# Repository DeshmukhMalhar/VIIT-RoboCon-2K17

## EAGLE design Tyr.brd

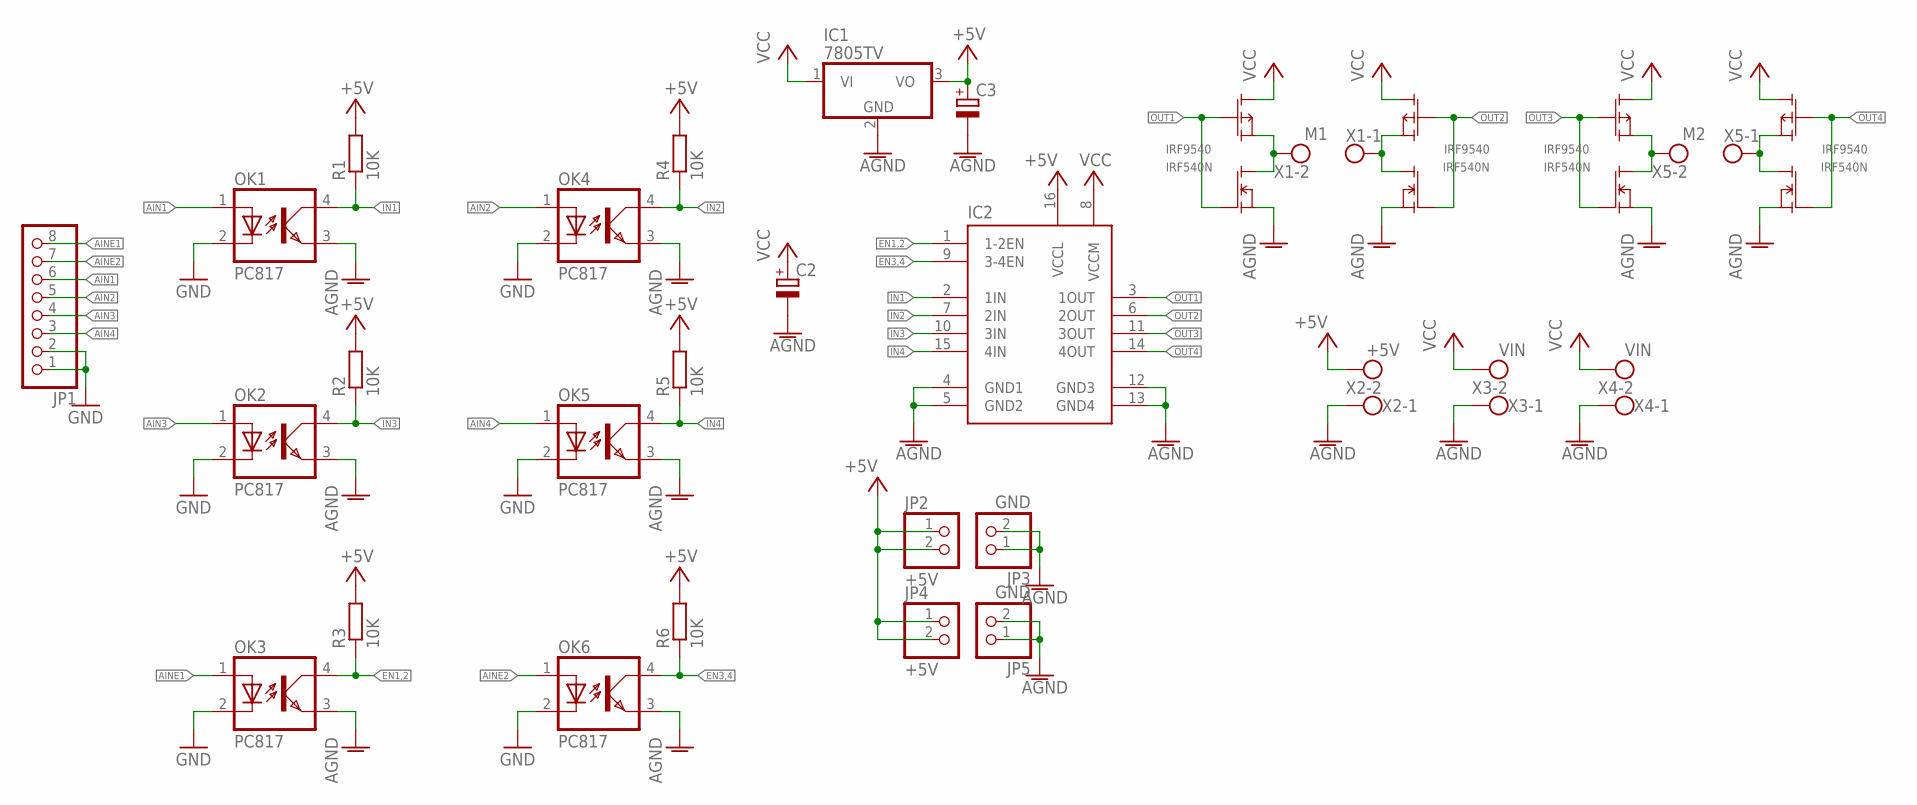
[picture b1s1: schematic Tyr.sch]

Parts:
C2: CPOL-EUE3.5-8; E3,5-8
C3: CPOL-EUE2-5; E2-5
IC1: 7805TV; TO220V
IC2: L293D; DIL16
JP1: PINHD-1X8; 1X08
JP2, JP4: +5V; 1X02
JP3, JP5: GND; 1X02
MOSFET1, MOSFET2, MOSFET3, MOSFET4: IRF540N; IRF9540
OK1, OK2, OK3, OK4, OK5, OK6: PC817; DIL04
P_MOSFET1, P_MOSFET2, P_MOSFET3, P_MOSFET4: IRF9540
R1, R2, R3, R4, R5, R6: 10K; 0207/7
X1: M1; W237-102
X2: +5V; W237-102
X3, X4: VIN; W237-102
X5: M2; W237-102

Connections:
+5V: C3.+, IC1.3 (VO), IC2.16 (VCCL), JP2.1, JP2.2, JP4.1, JP4.2, R1.2, R2.2, R3.2, R4.2, R5.2, R6.2, X2.2
AGND: C2.-, C3.-, IC1.2 (GND), IC2.4 (GND1), IC2.5 (GND2), IC2.12 (GND3), IC2.13 (GND4), JP3.1, JP3.2, JP5.1, JP5.2, MOSFET1.S, MOSFET2.S, MOSFET3.S, MOSFET4.S, OK1.3 (EMIT), OK2.3 (EMIT), OK3.3 (EMIT), OK4.3 (EMIT), OK5.3 (EMIT), OK6.3 (EMIT), X2.1, X3.1, X4.1
AIN1: JP1.6, OK1.1 (A)
AIN2: JP1.5, OK4.1 (A)
AIN3: JP1.4, OK2.1 (A)
AIN4: JP1.3, OK5.1 (A)
AINE1: JP1.8, OK3.1 (A)
AINE2: JP1.7, OK6.1 (A)
EN1,2: IC2.1 (1-2EN), OK3.4 (COL), R3.1
EN3,4: IC2.9 (3-4EN), OK6.4 (COL), R6.1
GND: JP1.1, JP1.2, OK1.2 (C), OK2.2 (C), OK3.2 (C), OK4.2 (C), OK5.2 (C), OK6.2 (C)
IN1: IC2.2 (1IN), OK1.4 (COL), R1.1
IN2: IC2.7 (2IN), OK4.4 (COL), R4.1
IN3: IC2.10 (3IN), OK2.4 (COL), R2.1
IN4: IC2.15 (4IN), OK5.4 (COL), R5.1
M1L: MOSFET1.D, P_MOSFET1.S, X1.2
M1R: MOSFET2.D, P_MOSFET2.S, X1.1
M2L: MOSFET3.D, P_MOSFET3.S, X5.2
M2R: MOSFET4.D, P_MOSFET4.S, X5.1
OUT1: IC2.3 (1OUT), MOSFET1.G, P_MOSFET1.G
OUT2: IC2.6 (2OUT), MOSFET2.G, P_MOSFET2.G
OUT3: IC2.11 (3OUT), MOSFET3.G, P_MOSFET3.G
OUT4: IC2.14 (4OUT), MOSFET4.G, P_MOSFET4.G
VCC: C2.+, IC1.1 (VI), IC2.8 (VCCM), P_MOSFET1.D, P_MOSFET2.D, P_MOSFET3.D, P_MOSFET4.D, X3.2, X4.2

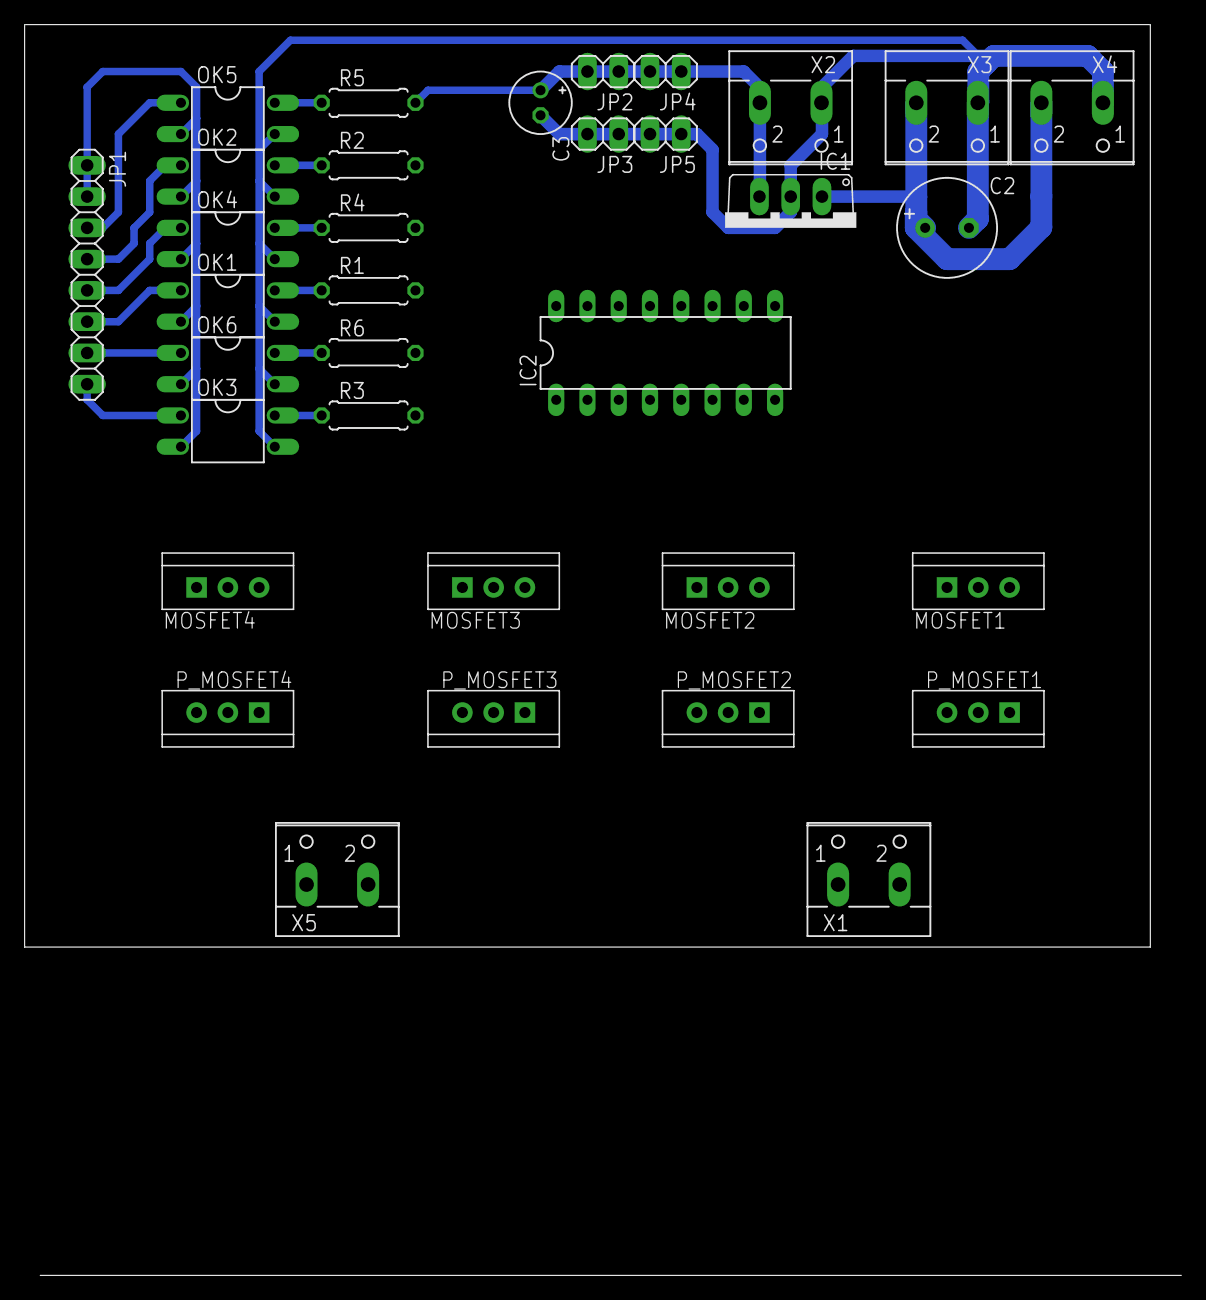
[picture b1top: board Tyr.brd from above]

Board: 2 copper layers, 91.4 x 74.9 mm, 34 parts (0 on the bottom side), 24 nets.

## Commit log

2017-01-18 first file
2017-01-18 Motor control using left analog stick of PS3 controller
    Motor control using Arduino, USB shield and PS3 controller.
    Shifting the Left analog stick right will move the motor backwards and vice-versa
    This works with Aniket Dhere's MOSFET driver-relay composite H-bridge
2017-01-22 2xH Bridge driver
    Eagle *.brd and *.sch for the MOSFET driver.
    Max current is 20A
2017-01-23 Higher Res/Freq PWM
2017-01-24 Batt Indicator PCB
    Author : Parag
    CC-by-SA
2017-01-24 updated batteryindicator
    parag
    pcd footprint updated
